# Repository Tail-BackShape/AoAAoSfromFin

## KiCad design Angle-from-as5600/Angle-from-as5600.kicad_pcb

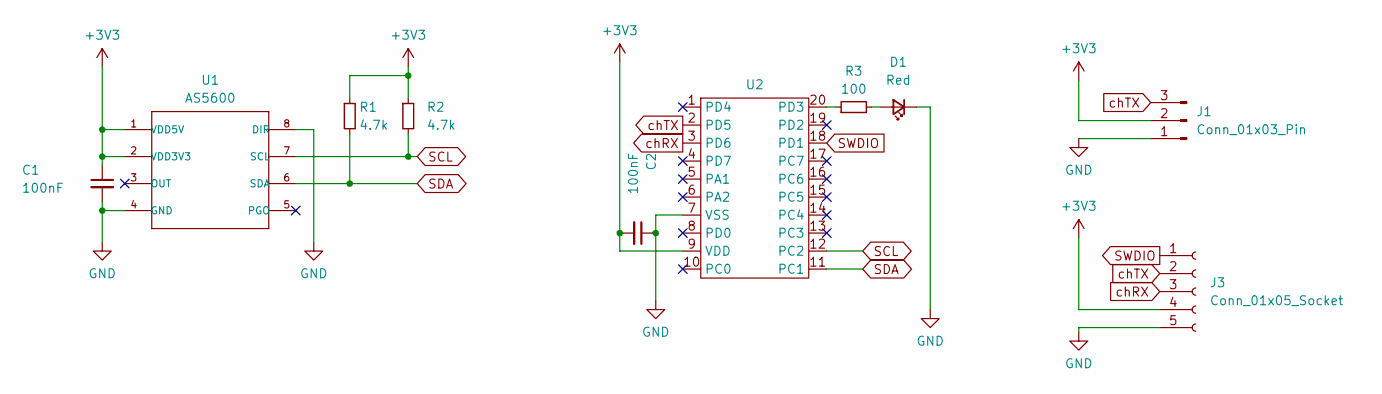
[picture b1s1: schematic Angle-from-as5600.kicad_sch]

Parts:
C1, C2: 100nF; C_0603_1608Metric_Pad1.08x0.95mm_HandSolder
D1: Red; D_0603_1608Metric_Pad1.05x0.95mm_HandSolder
J1: Conn_01x03_Pin; JST_XH_S3B-XH-A_1x03_P2.50mm_Horizontal
J3: Conn_01x05_Socket; PinHeader_1x05_P2.54mm_Horizontal
R1, R2: 4.7k; R_0603_1608Metric_Pad0.98x0.95mm_HandSolder
R3: 100; R_0603_1608Metric_Pad0.98x0.95mm_HandSolder
U1: AS5600
U2: SSOP-20_4.4x6.5mm_P0.65mm_bigpad

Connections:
+3V3: C1.1, C2.2, J1.2, J3.4, R1.1, R2.1, U1.1 (VDD5V), U1.2 (VDD3V3), U2.9 (VDD)
GND: C1.2, C2.1, D1.1 (K), J1.1, J3.5, U1.4 (GND), U1.8 (DIR), U2.7 (VSS)
unnamed: D1.2 (A), R3.2
unnamed: R3.1, U2.20 (PD3)
SCL: R2.2, U1.7 (SCL), U2.12 (PC2)
SDA: R1.2, U1.6 (SDA), U2.11 (PC1)
SWDIO: J3.1, U2.18 (PD1)
chRX: J3.3, U2.3 (PD6)
chTX: J1.3, J3.2, U2.2 (PD5)

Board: 2 copper layers, 10 parts (0 on the bottom side), 9 nets, no tracks yet.

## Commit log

2024-04-03 からあげ
2024-04-13 fix kicad files
    fix pin pitch
